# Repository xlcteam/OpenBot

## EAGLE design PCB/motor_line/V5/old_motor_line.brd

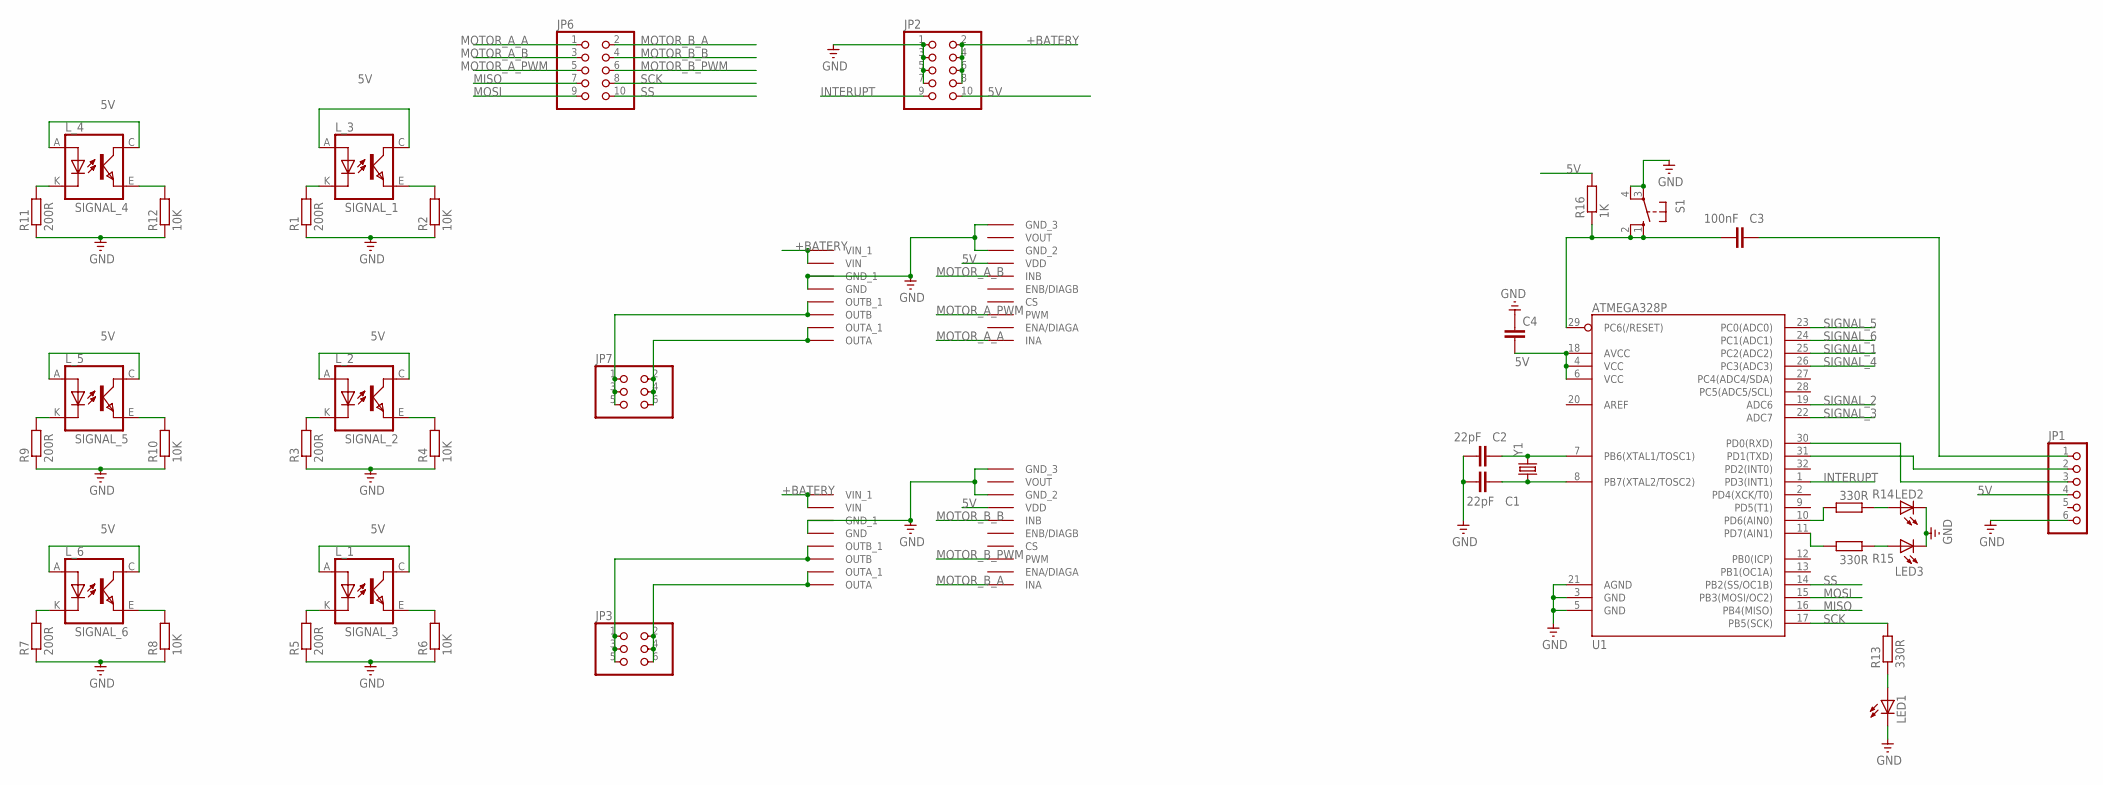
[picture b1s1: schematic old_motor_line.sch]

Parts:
C1, C2: 22pF; C0603
C3: 100nF; C0603
C4: C-EUC0603; C0603
JP1: PINHD-1X6/90; 1X06/90
JP2, JP6: PINHD-2X5IDC; 2X05_IDC
JP3, JP7: PINHD-2X3IDC; 2X03_IDC
LED1, LED2, LED3: LEDCHIPLED_0603; CHIPLED_0603
L_1, L_2, L_3, L_4, L_5, L_6: TCRT5000
R1, R3, R5, R7, R9, R11: 200R; R0603
R2, R4, R6, R8, R10, R12: 10K; R0603
R13, R14, R15: 330R; R0603
R16: 1K; R0603
S1: 10-XX; B3F-10XX
U1: ATMEGA328P; TQFP32-08
U$1, U$2: MOTOR_DRIVER
Y1: CRYSTALHC49US; HC49US

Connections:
5V: C4.2, JP1.4, JP2.10, L_1.A (ANODE), L_1.C (COLLECTOR), L_2.A (ANODE), L_2.C (COLLECTOR), L_3.A (ANODE), L_3.C (COLLECTOR), L_4.A (ANODE), L_4.C (COLLECTOR), L_5.A (ANODE), L_5.C (COLLECTOR), L_6.A (ANODE), L_6.C (COLLECTOR), R16.2, U1.4 (VCC), U1.6 (VCC), U1.18 (AVCC), U$1.VDD, U$2.VDD
+BATERY: JP2.2, JP2.4, JP2.6, JP2.8, U$1.VIN, U$1.VIN_1, U$2.VIN, U$2.VIN_1
GND: C1.1, C2.1, C4.1, JP1.6, JP2.1, JP2.3, JP2.5, JP2.7, LED1.C, LED2.C, LED3.C, R1.1, R2.1, R3.1, R4.1, R5.1, R6.1, R7.1, R8.1, R9.1, R10.1, R11.1, R12.1, S1.3, S1.4 (P1), U1.3 (GND), U1.5 (GND), U1.21 (AGND), U$1.GND, U$1.GND_1, U$1.GND_2, U$1.GND_3, U$2.GND, U$2.GND_1, U$2.GND_2, U$2.GND_3
INTERUPT: JP2.9, U1.1 (PD3(INT1))
MISO: JP6.7, U1.16 (PB4(MISO))
MOSI: JP6.9, U1.15 (PB3(MOSI/OC2))
MOTOR_1_1: JP7.1, JP7.3, JP7.5, U$1.OUTB, U$1.OUTB_1
MOTOR_1_2: JP7.2, JP7.4, JP7.6, U$1.OUTA, U$1.OUTA_1
MOTOR_2_1: JP3.2, JP3.4, JP3.6, U$2.OUTA, U$2.OUTA_1
MOTOR_2_2: JP3.1, JP3.3, JP3.5, U$2.OUTB, U$2.OUTB_1
MOTOR_A_A: JP6.1, U$1.INA
MOTOR_A_B: JP6.3, U$1.INB
MOTOR_A_PWM: JP6.5, U$1.PWM
MOTOR_B_A: JP6.2, U$2.INA
MOTOR_B_B: JP6.4, U$2.INB
MOTOR_B_PWM: JP6.6, U$2.PWM
unnamed: L_3.K (CATHODE), R1.2
unnamed: L_2.K (CATHODE), R3.2
unnamed: L_1.K (CATHODE), R5.2
unnamed: L_6.K (CATHODE), R7.2
unnamed: L_5.K (CATHODE), R9.2
unnamed: L_4.K (CATHODE), R11.2
unnamed: C2.2, U1.7 (PB6(XTAL1/TOSC1)), Y1.2
unnamed: C1.2, U1.8 (PB7(XTAL2/TOSC2)), Y1.1
unnamed: JP1.3, U1.30 (PD0(RXD))
unnamed: JP1.2, U1.31 (PD1(TXD))
unnamed: C3.2, JP1.1
unnamed: C3.1, R16.1, S1.1 (S), S1.2 (S1), U1.29 (PC6(/RESET))
unnamed: LED1.A, R13.1
unnamed: LED2.A, R14.1
unnamed: R15.2, U1.11 (PD7(AIN1))
unnamed: LED3.A, R15.1
unnamed: R14.2, U1.10 (PD6(AIN0))
SCK: JP6.8, R13.2, U1.17 (PB5(SCK))
SIGNAL_1: L_3.E (EMITTER), R2.2, U1.25 (PC2(ADC2))
SIGNAL_2: L_2.E (EMITTER), R4.2, U1.19 (ADC6)
SIGNAL_3: L_1.E (EMITTER), R6.2, U1.22 (ADC7)
SIGNAL_4: L_4.E (EMITTER), R12.2, U1.26 (PC3(ADC3))
SIGNAL_5: L_5.E (EMITTER), R10.2, U1.23 (PC0(ADC0))
SIGNAL_6: L_6.E (EMITTER), R8.2, U1.24 (PC1(ADC1))
SS: JP6.10, U1.14 (PB2(SS/OC1B))

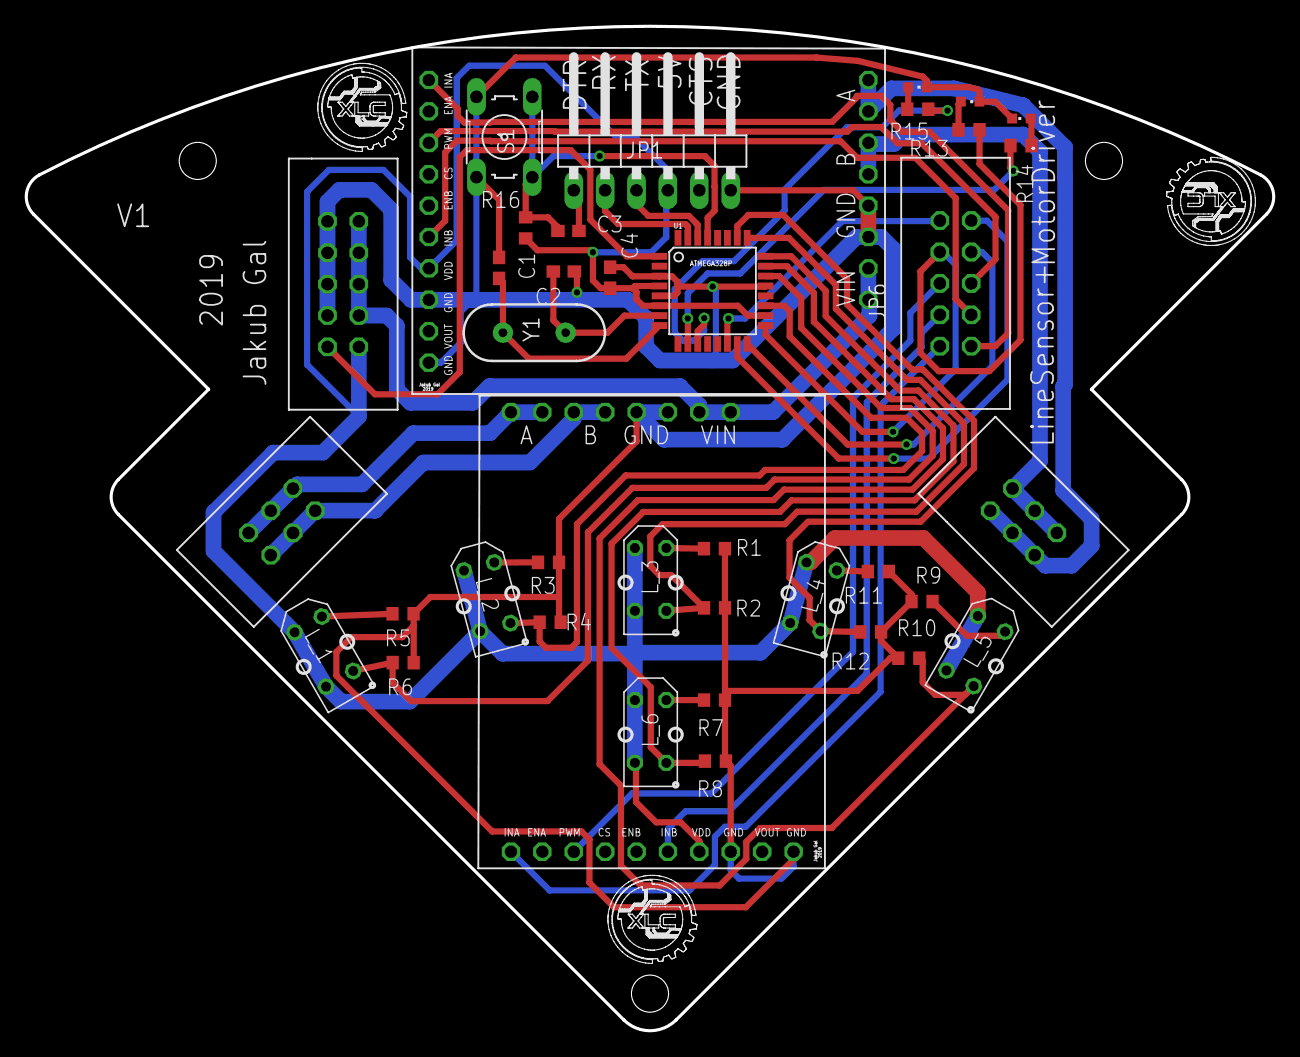
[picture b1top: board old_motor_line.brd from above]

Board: 2 copper layers, 100.9 x 81.3 mm, 39 parts (0 on the bottom side), 41 nets.

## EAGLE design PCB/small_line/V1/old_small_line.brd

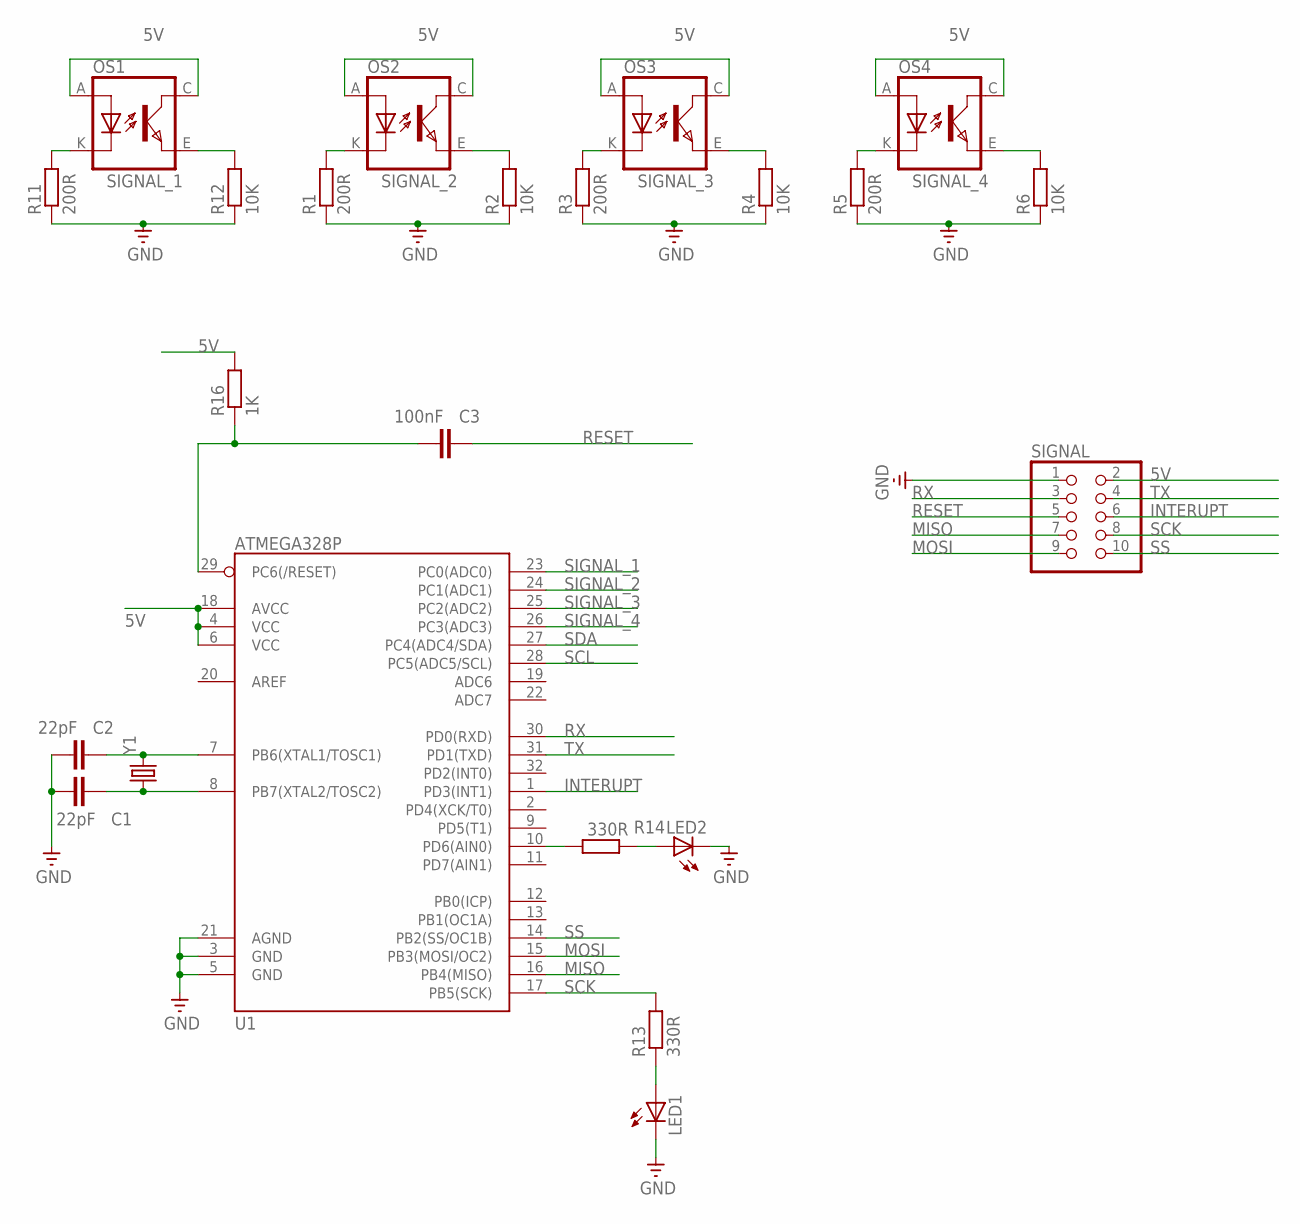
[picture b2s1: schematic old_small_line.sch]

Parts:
C1, C2: 22pF; C0603
C3: 100nF; C0603
LED1, LED2: LEDCHIPLED_0603; CHIPLED_0603
OS1, OS2, OS3, OS4: TCRT5000
R1, R3, R5, R11: 200R; R0603
R2, R4, R6, R12: 10K; R0603
R13, R14: 330R; R0603
R16: 1K; R0603
SIGNAL: PINHD-2X5; 2X05
U1: ATMEGA328P; TQFP32-08
Y1: CRYSTALHC49US; HC49US

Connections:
5V: OS1.A (ANODE), OS1.C (COLLECTOR), OS2.A (ANODE), OS2.C (COLLECTOR), OS3.A (ANODE), OS3.C (COLLECTOR), OS4.A (ANODE), OS4.C (COLLECTOR), R16.2, SIGNAL.2, U1.4 (VCC), U1.6 (VCC), U1.18 (AVCC)
GND: C1.1, C2.1, LED1.C, LED2.C, R1.1, R2.1, R3.1, R4.1, R5.1, R6.1, R11.1, R12.1, SIGNAL.1, U1.3 (GND), U1.5 (GND), U1.21 (AGND)
INTERUPT: SIGNAL.6, U1.1 (PD3(INT1))
MISO: SIGNAL.7, U1.16 (PB4(MISO))
MOSI: SIGNAL.9, U1.15 (PB3(MOSI/OC2))
unnamed: OS2.K (CATHODE), R1.2
unnamed: OS3.K (CATHODE), R3.2
unnamed: OS4.K (CATHODE), R5.2
unnamed: OS1.K (CATHODE), R11.2
unnamed: C2.2, U1.7 (PB6(XTAL1/TOSC1)), Y1.2
unnamed: C1.2, U1.8 (PB7(XTAL2/TOSC2)), Y1.1
unnamed: C3.1, R16.1, U1.29 (PC6(/RESET))
unnamed: LED1.A, R13.1
unnamed: LED2.A, R14.1
unnamed: R14.2, U1.10 (PD6(AIN0))
RESET: C3.2, SIGNAL.5
RX: SIGNAL.3, U1.30 (PD0(RXD))
SCK: R13.2, SIGNAL.8, U1.17 (PB5(SCK))
SCL: U1.28 (PC5(ADC5/SCL))
SDA: U1.27 (PC4(ADC4/SDA))
SIGNAL_1: OS1.E (EMITTER), R12.2, U1.23 (PC0(ADC0))
SIGNAL_2: OS2.E (EMITTER), R2.2, U1.24 (PC1(ADC1))
SIGNAL_3: OS3.E (EMITTER), R4.2, U1.25 (PC2(ADC2))
SIGNAL_4: OS4.E (EMITTER), R6.2, U1.26 (PC3(ADC3))
SS: SIGNAL.10, U1.14 (PB2(SS/OC1B))
TX: SIGNAL.4, U1.31 (PD1(TXD))

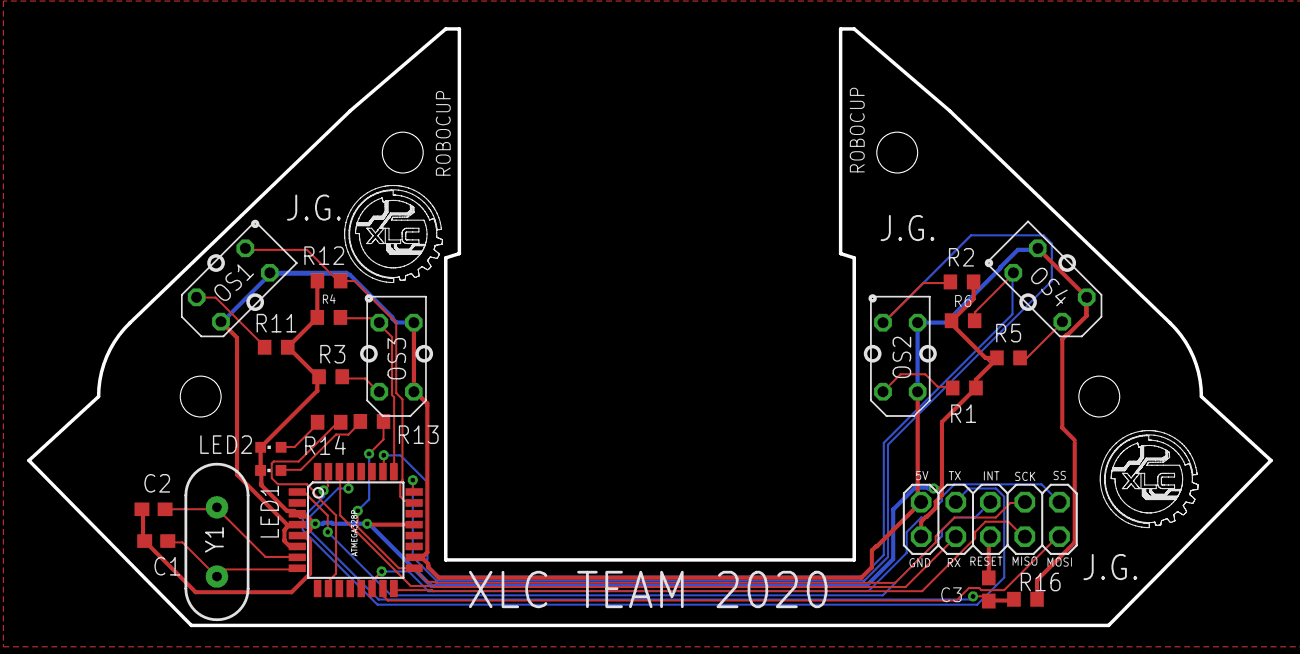
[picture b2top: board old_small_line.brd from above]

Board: 2 copper layers, 91.2 x 43.8 mm, 23 parts (0 on the bottom side), 24 nets.

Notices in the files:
parts and their libraries:
SparkFun-DigitalIC: Licensing: CC v3.0 Share-Alike You are welcome to use this library for commercial purposes.
